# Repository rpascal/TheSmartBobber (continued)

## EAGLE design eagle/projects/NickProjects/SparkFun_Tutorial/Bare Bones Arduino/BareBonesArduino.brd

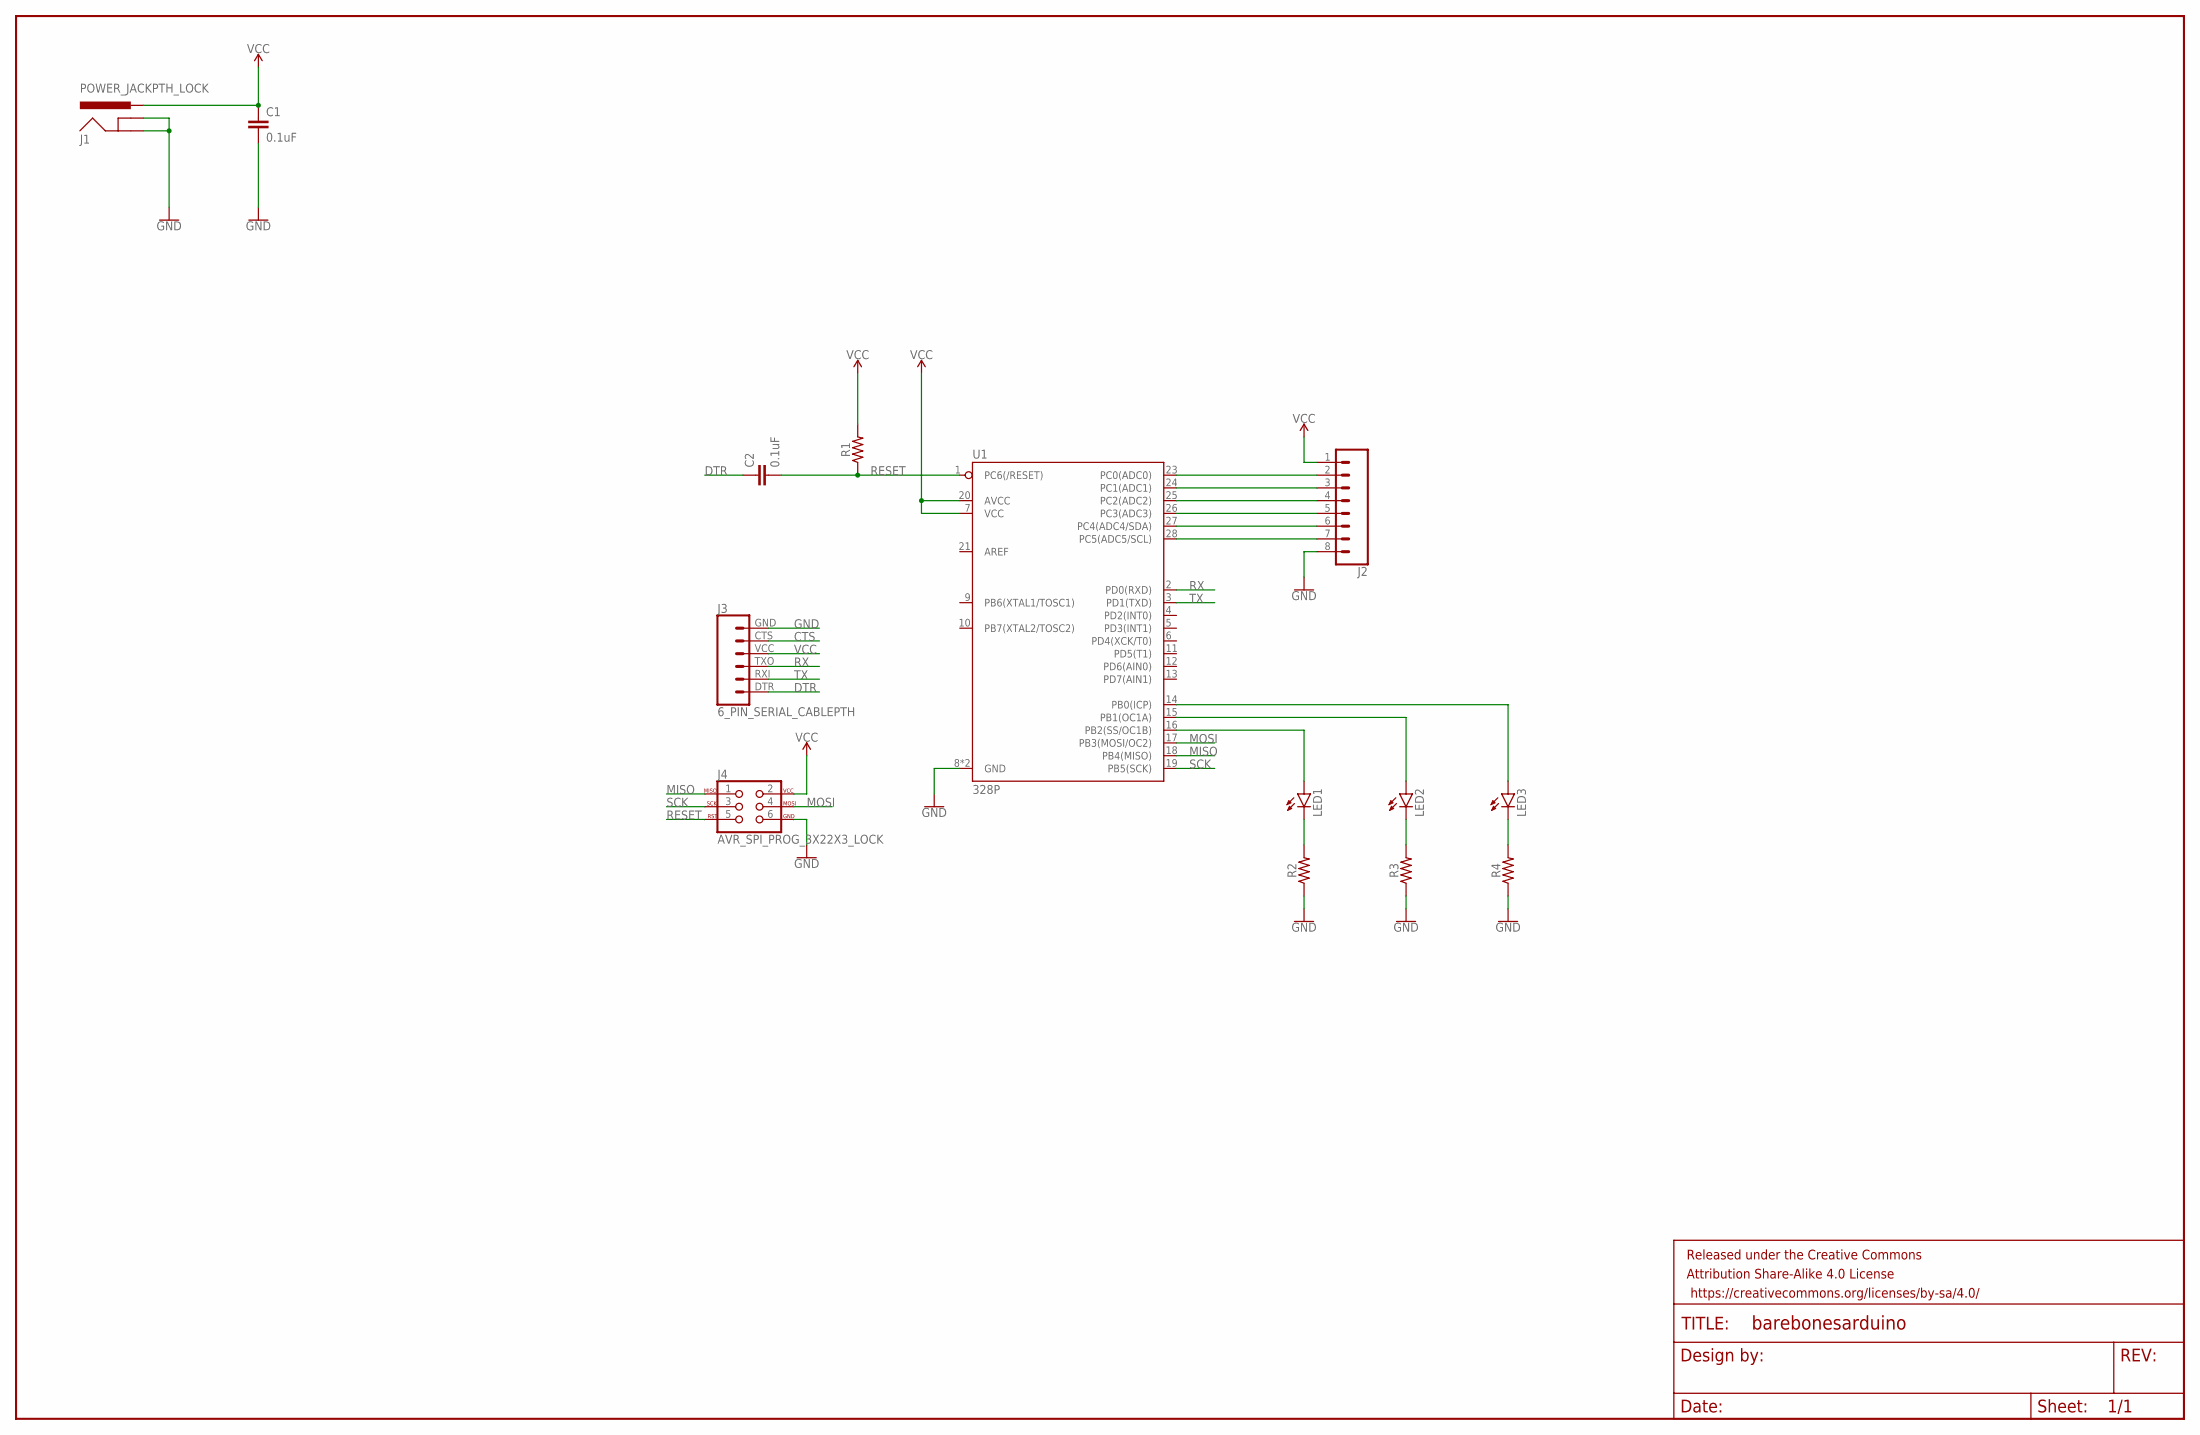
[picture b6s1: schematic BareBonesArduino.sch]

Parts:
C1, C2: 0.1uF; CAP-PTH-SMALL-KIT
FRAME1: FRAME-LEDGER; CREATIVE_COMMONS
J1: POWER_JACKPTH_LOCK; POWER_JACK_PTH_LOCK
J2: CONN_08"; 1X08
J3: 6_PIN_SERIAL_CABLEPTH; FTDI_BASIC
J4: AVR_SPI_PROG_3X22X3_LOCK; 2X3_LOCK
LED1, LED2, LED3: LED5MM
R1, R2, R3, R4: AXIAL-0.3
U1: 328P; DIP28

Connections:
CTS: J3.CTS (5)
DTR: C2.1, J3.DTR (1)
GND: C1.2, J1.GND, J1.GNDBREAK, J2.8, J3.GND (6), J4.6, R2.P$1 (1), R3.P$1 (1), R4.P$1 (1), U1.8 (GND), U1.22 (GND)
MISO: J4.1, U1.18 (PB4(MISO))
MOSI: J4.4, U1.17 (PB3(MOSI/OC2))
unnamed: J2.2, U1.23 (PC0(ADC0))
unnamed: J2.3, U1.24 (PC1(ADC1))
unnamed: J2.4, U1.25 (PC2(ADC2))
unnamed: J2.5, U1.26 (PC3(ADC3))
unnamed: J2.6, U1.27 (PC4(ADC4/SDA))
unnamed: J2.7, U1.28 (PC5(ADC5/SCL))
unnamed: LED3.A, U1.14 (PB0(ICP))
unnamed: LED2.A, U1.15 (PB1(OC1A))
unnamed: LED1.A, U1.16 (PB2(SS/OC1B))
unnamed: LED1.K (C), R2.P$2 (2)
unnamed: LED2.K (C), R3.P$2 (2)
unnamed: LED3.K (C), R4.P$2 (2)
RESET: C2.2, J4.5, R1.P$1 (1), U1.1 (PC6(/RESET))
RX: J3.TXO (3), U1.2 (PD0(RXD))
SCK: J4.3, U1.19 (PB5(SCK))
TX: J3.RXI (2), U1.3 (PD1(TXD))
VCC: C1.1, J1.PWR, J2.1, J3.VCC (4), J4.2, R1.P$2 (2), U1.7 (VCC), U1.20 (AVCC)

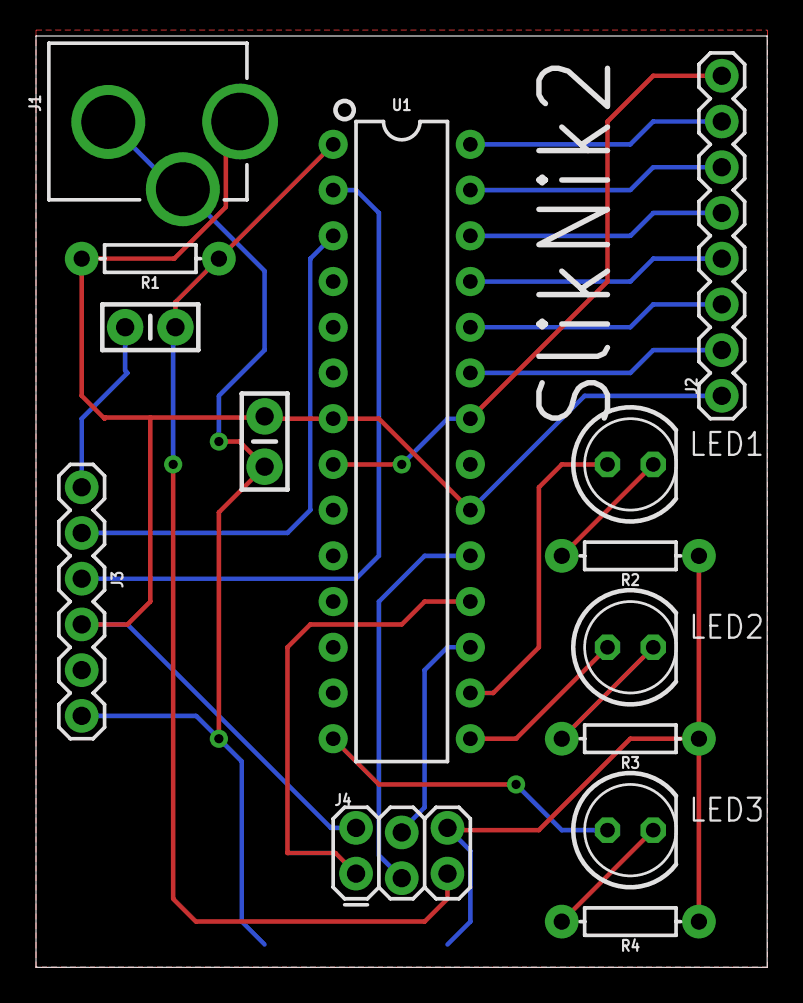
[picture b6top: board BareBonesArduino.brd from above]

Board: 2 copper layers, 40.6 x 51.7 mm, 15 parts (0 on the bottom side), 21 nets.

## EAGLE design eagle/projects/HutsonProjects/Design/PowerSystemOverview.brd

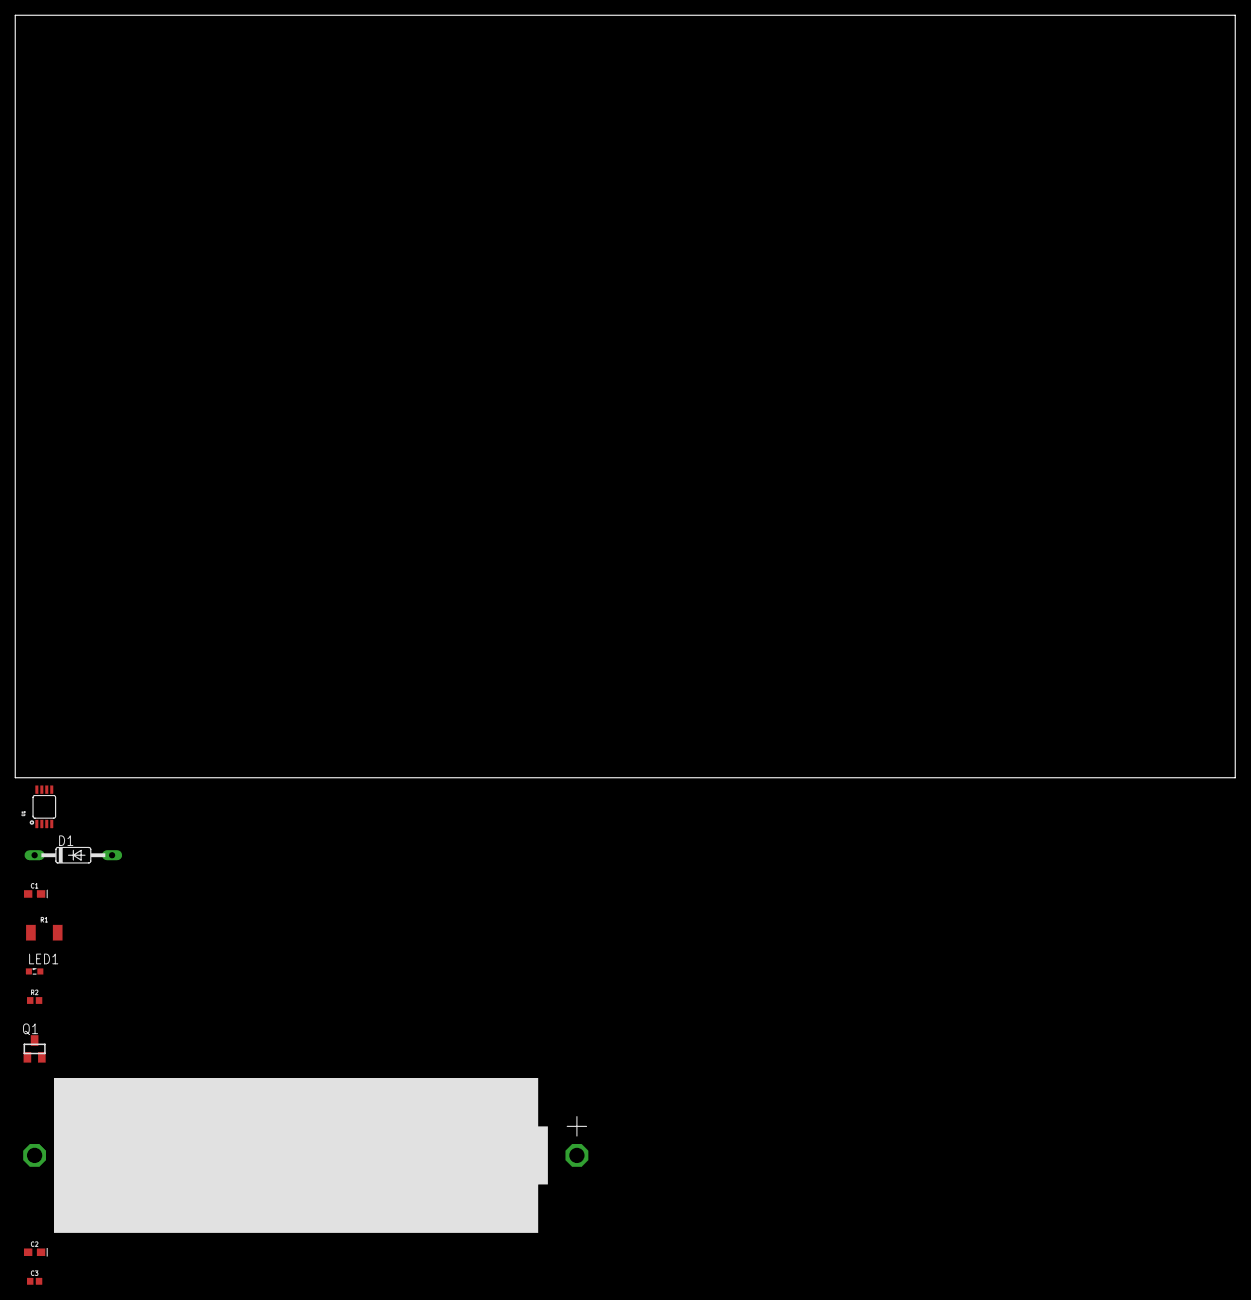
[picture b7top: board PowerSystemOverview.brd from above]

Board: 2 copper layers, 160.0 x 100.0 mm, 10 parts (0 on the bottom side), 8 nets, no tracks yet.

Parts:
C1, C2: 10uF; 0603-POLAR
C3: 0.1uF; 0402
D1: 1N4148DO35-10; DO35-10
LED1: LED_SML0603
Q1: FDN360P; SUPER-SOT3
R1: 0.1; 1210
R2: 100K; 0402
U1: MCP7384XX; MSOP8
U$1: 18650PTH; 18650-CASE-PTH

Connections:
GND: C1.-, C2.-, C3.2, U1.6, U$1.NEG
unnamed: Q1.2, R1.2, U1.1
unnamed: Q1.1, U1.8
unnamed: C1.+, D1.C, LED1.A, R1.1, R2.1, U1.2
unnamed: R2.2, U1.4
unnamed: LED1.C, U1.3
unnamed: C3.1, U1.5
unnamed: C2.+, Q1.3, U1.7, U$1.POS

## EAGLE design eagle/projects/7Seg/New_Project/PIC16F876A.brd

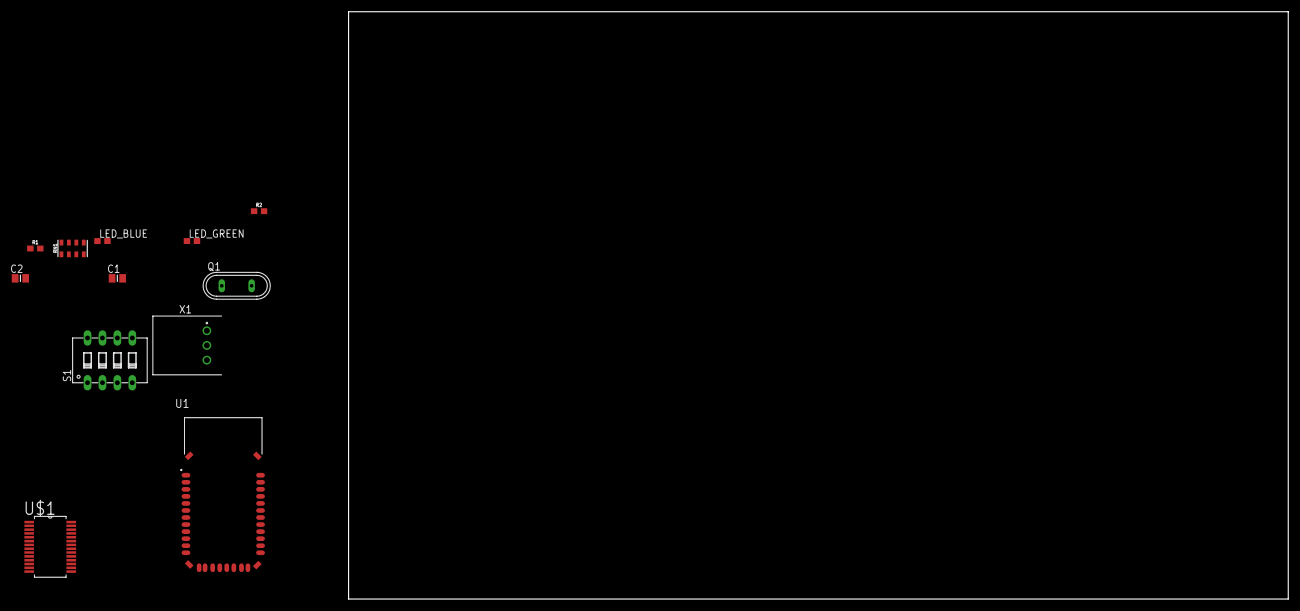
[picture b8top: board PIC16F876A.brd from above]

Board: 2 copper layers, 160.0 x 100.0 mm, 12 parts (0 on the bottom side), 13 nets, no tracks yet.

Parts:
C1, C2: 08052U220JAT2A; CAPC2012X140N
LED_BLUE: LTST-C190TBKT; 0603
LED_GREEN: LTST-C190KGKT; 0603
Q1: QS
R1, R2: 220; 0603
RN1: 1k; 0805-ARV
S1: DIP04YL
U1: RN41-I/RM; XCVR_RN42-I/RM
U$1: PIC16LF876A-I/SS; SOP254P785X200-28N
X1: S3B-XH-A(LF)(SN)

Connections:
GND: C1.2, C2.2, R2.1, U1.1, U1.12, U1.28, U1.29, U$1.8, U$1.19
unnamed: LED_GREEN.1, R1.2
unnamed: LED_BLUE.1, R2.2
unnamed: RN1.2, S1.5
unnamed: RN1.3, S1.6
unnamed: RN1.4, S1.7
unnamed: RN1.1, S1.8
OSC1: C2.1, Q1.1, U$1.9
OSC2: C1.1, Q1.2, U$1.10
PI02: LED_BLUE.2, U1.19
PI05: R1.1, U1.21
SHIELD: U1.S1, U1.S2, U1.S3, U1.S4
VDD: LED_GREEN.2, U1.11, U$1.20

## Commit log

2018-10-24 Adding android capacitor
2018-10-24 clean up errors
2018-10-24 adding PWA support
2018-10-24 adding some basic command in package json
2018-10-24 making it work on laptop
2018-10-25 rename home page to real-time information page
2018-10-25 rename contact to controls
2018-10-25 rename to log
2018-10-25 updating config xml
2018-10-26 adding dark theme
2018-10-29 change up folder structue a tad.
2018-10-29 starts of bluetooth
2018-10-31 adding bluetooth code
2018-11-01 temp code
2018-11-01 prep for new connection page
2018-11-01 adding toast service
2018-11-02 adding better navigation, wrap chnaging of subjects in zone so view can update properly
2018-11-03 clean up
2018-11-09 clean up some shit
2019-01-11 making work on desktop
2019-01-20 Adding component for messages
2019-01-20 Adding weather data
2019-01-20 Move code to proper lifecycle
2019-01-21 Latest build
2019-01-21 moving app to own folder
2019-01-22 Adding embedded code
2019-01-22 Create config.h
    config.h file for the PWM file
2019-01-24 Adding component to view logs
2019-01-24 rename classes. clean up code.
2019-01-24 regenerate android
2019-01-24 testing shit out
    testing shit out
2019-01-24 Adding a way to communicate with the bobber correctly
2019-01-24 PWM
    Update
2019-01-25 Clean up/ auto connect
2019-01-26 Mock bluetooth provider
2019-01-26 Adding firebase
2019-01-27 Adding basic chart for bites
2019-01-28 Dynamically adding items to line chart
2019-01-28 Updated the ADC
2019-01-28 Deleted Test Files
2019-01-29 LInk bite data to graph
2019-01-29 fix checking cordova for providers
2019-01-29 Fancy graph
2019-01-29 Updated ADC Code
2019-01-31 Main Code PIC16LF876A
2019-01-31 Project Rename
2019-01-31 Main Clean Up
2019-01-31 Change way to handle uart inputs
2019-01-31 Change_Inputs Update
2019-01-31 Update 2
2019-01-31 Fixed NO_INPUT error
    Could not generatre code (prototybe)
2019-02-01 Update 1
2019-02-02 Updated Main ADC Code for Changes
    Included PWM, and Logic that Ryan helped med with
2019-02-02 Update 1,8
    1023!!!!!!
2019-02-03 adding a settings popover and removing controls tab
2019-02-03 Adding start of multiple themes
2019-02-03 Adding manully connecting and showing connection status in popover
2019-02-03 Removing unneeded
2019-02-04 Adding create new log page
2019-02-05 Persist log even when closing app
2019-02-05 adding location services
2019-02-05 Adding starts of display logs
2019-02-05 Updates to C, Need to implement running sum
2019-02-05 Update 2.0
    ADC Average function implemented and working! Will need to be cleaned up.
2019-02-05 2.1
    More updates yo
2019-02-06 making logs look better
2019-02-06 Adding code for reading solenoid
2019-02-06 Properly show logs
2019-02-06 Adding some changes to abstract out the bite values logic
2019-02-07 basic clean
2019-02-07 refactor managing average
2019-02-07 add weather to home and update app name on device
2019-02-07 Nick_Update
    Corrected .h file
2019-02-07 adding sounds
2019-02-07 adding images
2019-02-07 adding cloud functions
2019-02-07 Adding slides and moving take picture to toolbar
2019-02-10 fix up cloud function and make images show up on logs
2019-02-10 When solenoid is told to turn on keep on for X seconds and then turn back off
2019-02-10 send messages about when solenoid is on or off
2019-02-11 Create EAGLE
2019-02-11 Adding Eagle
2019-02-11 fix eagle
2019-02-11 adding readme for eagl
2019-02-11 Adding Hutson to EAGLE
2019-02-11 Add Resistor Test
2019-02-12 Added Surface Mount Schottky Diodes to Schematic
2019-02-12 Pyle Projects
2019-02-12 File Clean Up
2019-02-12 refactor bites to use a confirmed bit message
2019-02-13 EAGLE tutorial .sch
2019-02-13 Eagle tutorial complete
2019-02-13 fix slide a bit and adding average temp count
2019-02-13 Added 0.1mohm chip resistor
2019-02-13 100kohm chip resistor created
2019-02-13 PWM Set to 2.7kHz @ 50% Duty Cycle
2019-02-13 330 ohm chip resistor added
2019-02-13 2.7k chip resistor added
2019-02-14 Bullshit
2019-02-14 USB Mini Power In and New Resistor
2019-02-14 330 ohm resistor chip
2019-02-14 2.7k chip resistor
2019-02-14 Comment Out Ryan Code
2019-02-14 Ryan Commit Out stuff
2019-02-14 Capacitor Chips Added
2019-02-14 22 uf chip capacitor created
2019-02-14 2.2 uF capacitor chip added
2019-02-14 Deleted Outlines for circuit optimization
2019-02-14 SOLENOID WORKING
2019-02-14 SPDT added to circuit
2019-02-14 Frame added to PCB tutorial
2019-02-14 adding parts
2019-02-14 show uncategorized images
2019-02-14 Go back to code by ryan that nick fucked
2019-02-14 basic clean up
2019-02-17 Eagle Tutorial
2019-02-17 Wiring up tutorial through hole circuit
2019-02-17 Wiring Tutorial Circuit
2019-02-17 Wiring Tutorial Through Hole Schematic
2019-02-17 RN-41 Rev 2
2019-02-17 Wiring tutorial finished
2019-02-21 Changed PIO4 to PIO2
2019-02-21 remove shit
2019-02-21 Make adc compile
2019-02-21 if solenoid on dont turn back on for x seconds
2019-02-21 adding counter files
2019-02-21 kinda works for testing
2019-02-21 fix brokend thing
2019-02-22 TImer1 configured - Nick
2019-02-24 Make use of counter
2019-02-25 Updating bite graph
2019-02-25 Adding temp of water to home page
2019-02-25 LED Output Redefind
2019-02-27 RN41Board UPDATE
2019-02-27 Adding loader for aasync image and turn off animations on graph
2019-02-27 RN41 Board UPDATE
2019-02-28 Adding service for netowrk
2019-02-28 make counter work
2019-02-28 PCB tutorial/PCB layout intial
2019-03-01 Dimensions
2019-03-01 Addin in lab changes
2019-03-01 routing
2019-03-01 finished routing
2019-03-01 Fusion 360 Tutorial Model
2019-03-01 motherBoard Embedded Update
2019-03-01 Clean up for some speeds. Add tabs on logs page
2019-03-02 Clean up and save state of some config settings
2019-03-02 Secret
2019-03-02 Motherboard Design
2019-03-02 File Seperation buecausae Nick is a fucking dumbass
2019-03-02 Motherboard - Zach
2019-03-02 RN41 Updates
2019-03-02 RN41 Update
2019-03-03 Update RN41
2019-03-03 Power - Hutson
2019-03-03 Power Schematic
2019-03-03 RN-41 Complete
2019-03-03 Board update
2019-03-04 Power-Schematic
2019-03-04 motherboard_Power
2019-03-05 fix audio"
2019-03-05 Cleaning read temp
2019-03-05 ehatever
2019-03-05 Stash Push From Nick
2019-03-05 improving slides on log page
2019-03-05 bootstrap
2019-03-05 code update
2019-03-06 Finishing up carousels
2019-03-06 fix bootstrap overlay issues
2019-03-07 fix solenoid
2019-03-07 Fix not activating solenoid on initial
2019-03-11 MCP73831
2019-03-11 FS8205
2019-03-11 save state of led and autohook. Fix log line break. send data to bobber on load
2019-03-12 pART PRACRTICE
2019-03-12 Resistor
2019-03-12 WNER50FET Resistor
2019-03-12 New Resistor
2019-03-13 OSHPark .dru and RN-41 Update
2019-03-13 Move logic to proper location
2019-03-14 WE;SADOHGSAGDVNRIOWUE
2019-03-14 Part Fix
2019-03-14 Components
2019-03-14 I'm going through changes
2019-03-14 Board make
2019-03-14 Error Fix
2019-03-16 motherBoard
2019-03-19 File Updates
2019-03-19 motherBoard V1
2019-03-20 Led Part and Board Update
2019-03-20 Schematic Update
2019-03-20 update schematic and board
2019-03-21 boad update
2019-03-21 CRAZY UPDATE
2019-03-21 fuck fuck fuck fuck fuck fuck
2019-03-21 UPDATES!!!
2019-03-21 Hutson Fix
2019-03-21 Board Done!
2019-03-24 Cap Update
2019-03-25 PCBS ARE FUCKING DONE
2019-03-25 Board Astetcis Update
2019-03-25 Gerber Files
2019-04-10 afas
2019-04-18 Updating app shit
2019-04-18 Hide in setting
2019-04-20 Finisihing touched... maybe lol
2019-04-20 Change title
2019-04-22 UART Comment update
2019-04-24 Final Update
2019-04-29 Make bluetooth no t crash
2019-05-04 STL Files
